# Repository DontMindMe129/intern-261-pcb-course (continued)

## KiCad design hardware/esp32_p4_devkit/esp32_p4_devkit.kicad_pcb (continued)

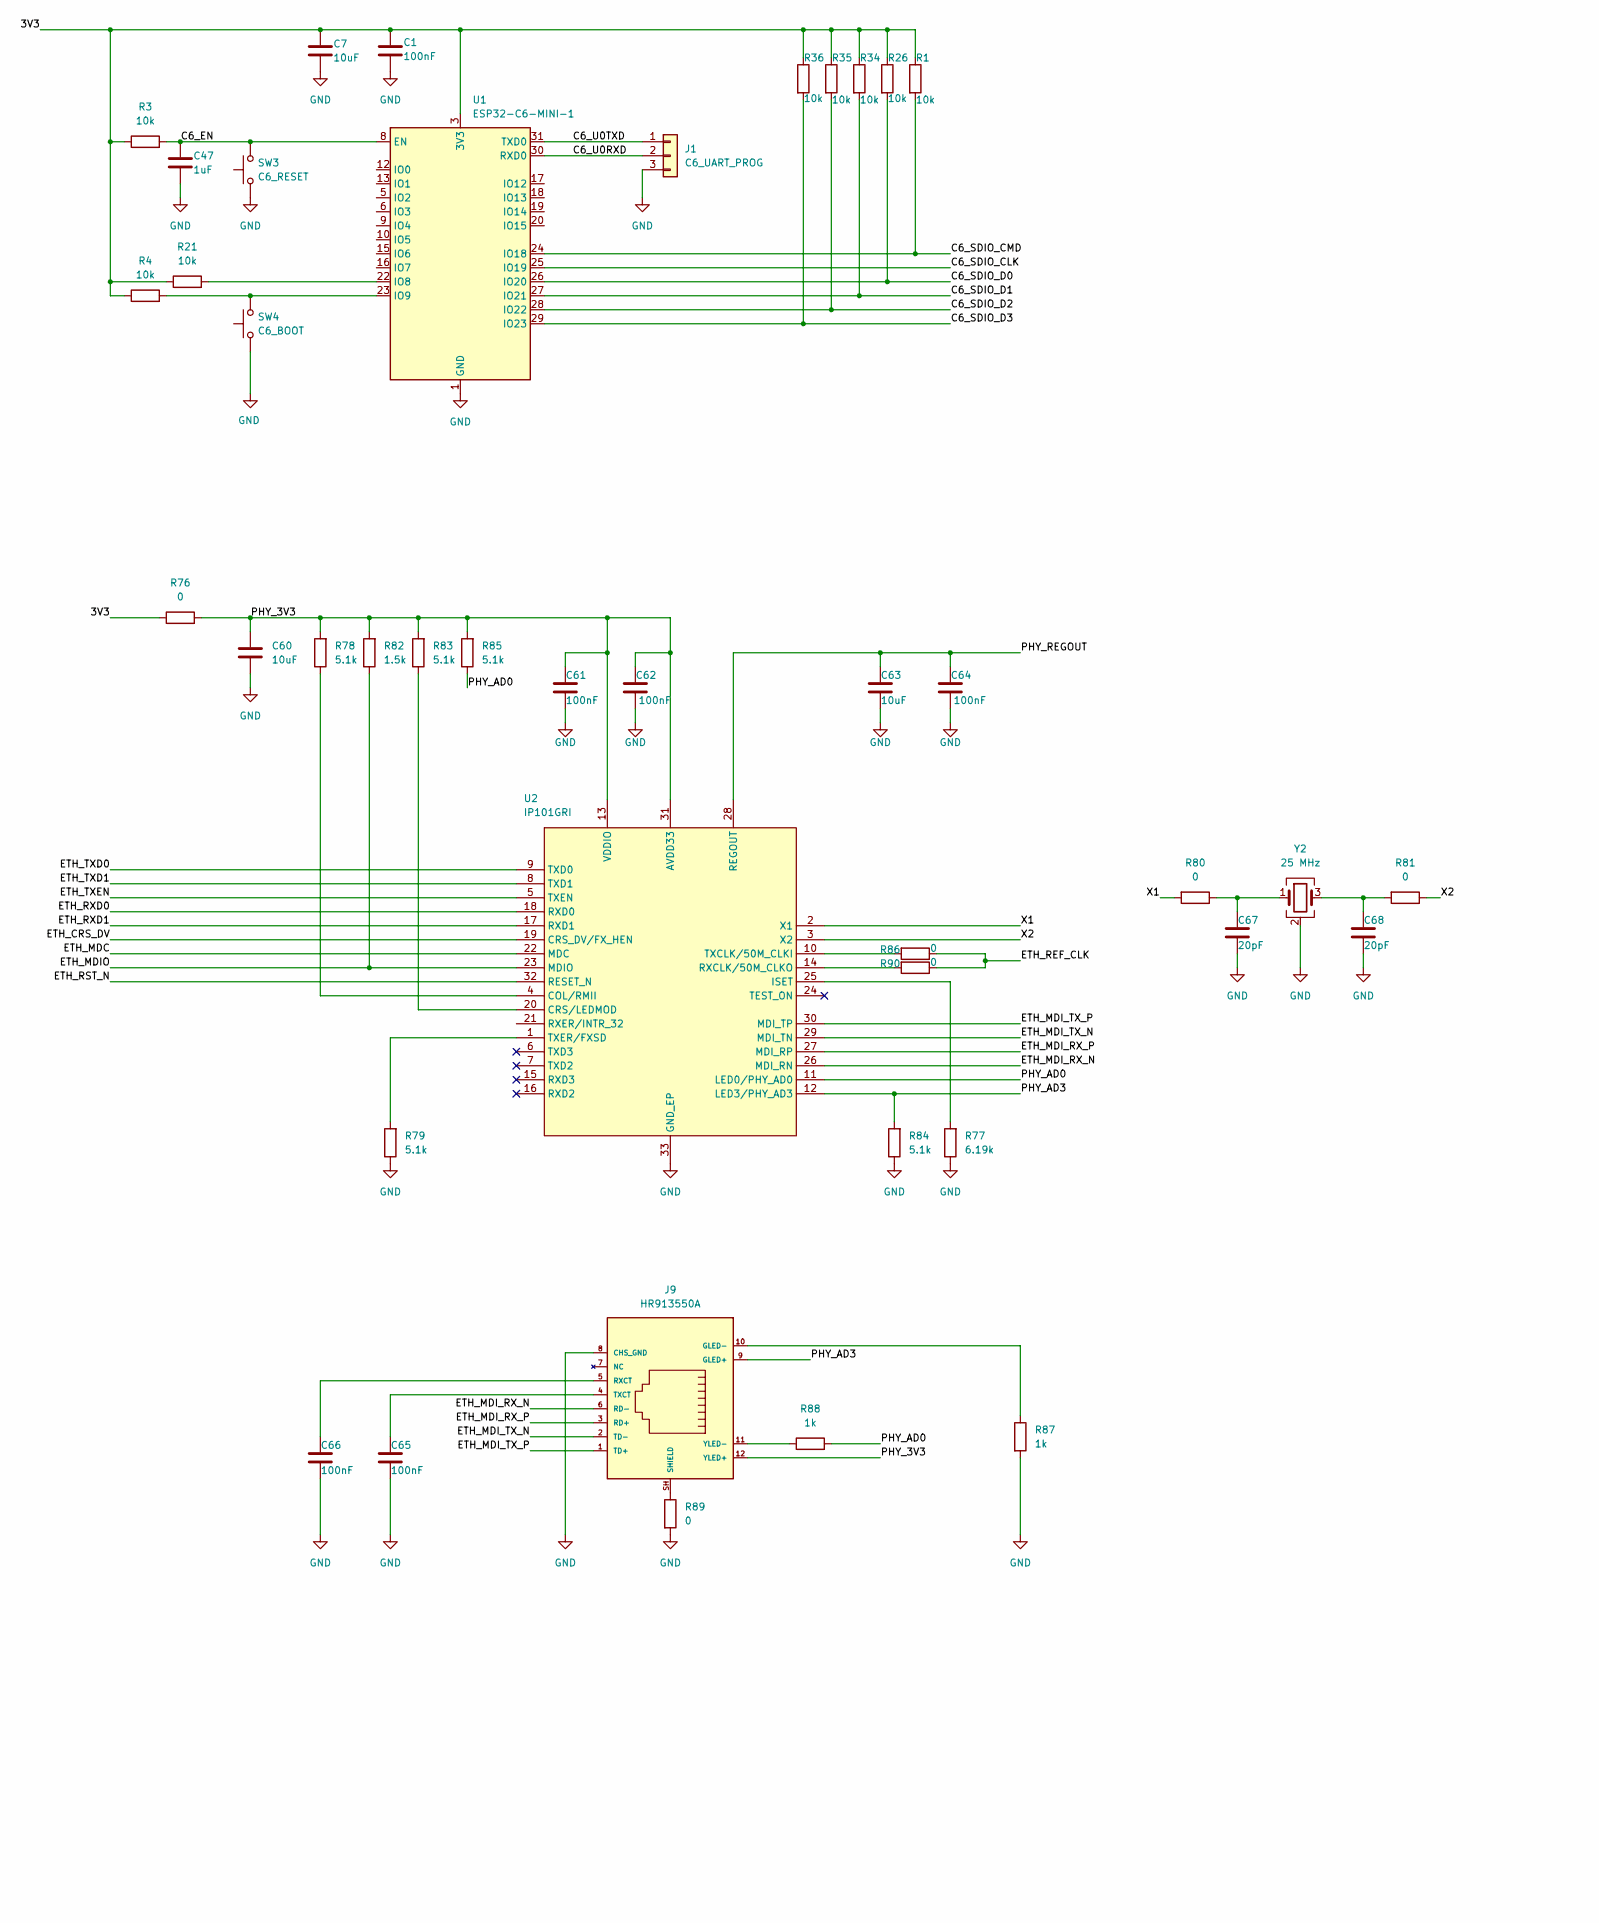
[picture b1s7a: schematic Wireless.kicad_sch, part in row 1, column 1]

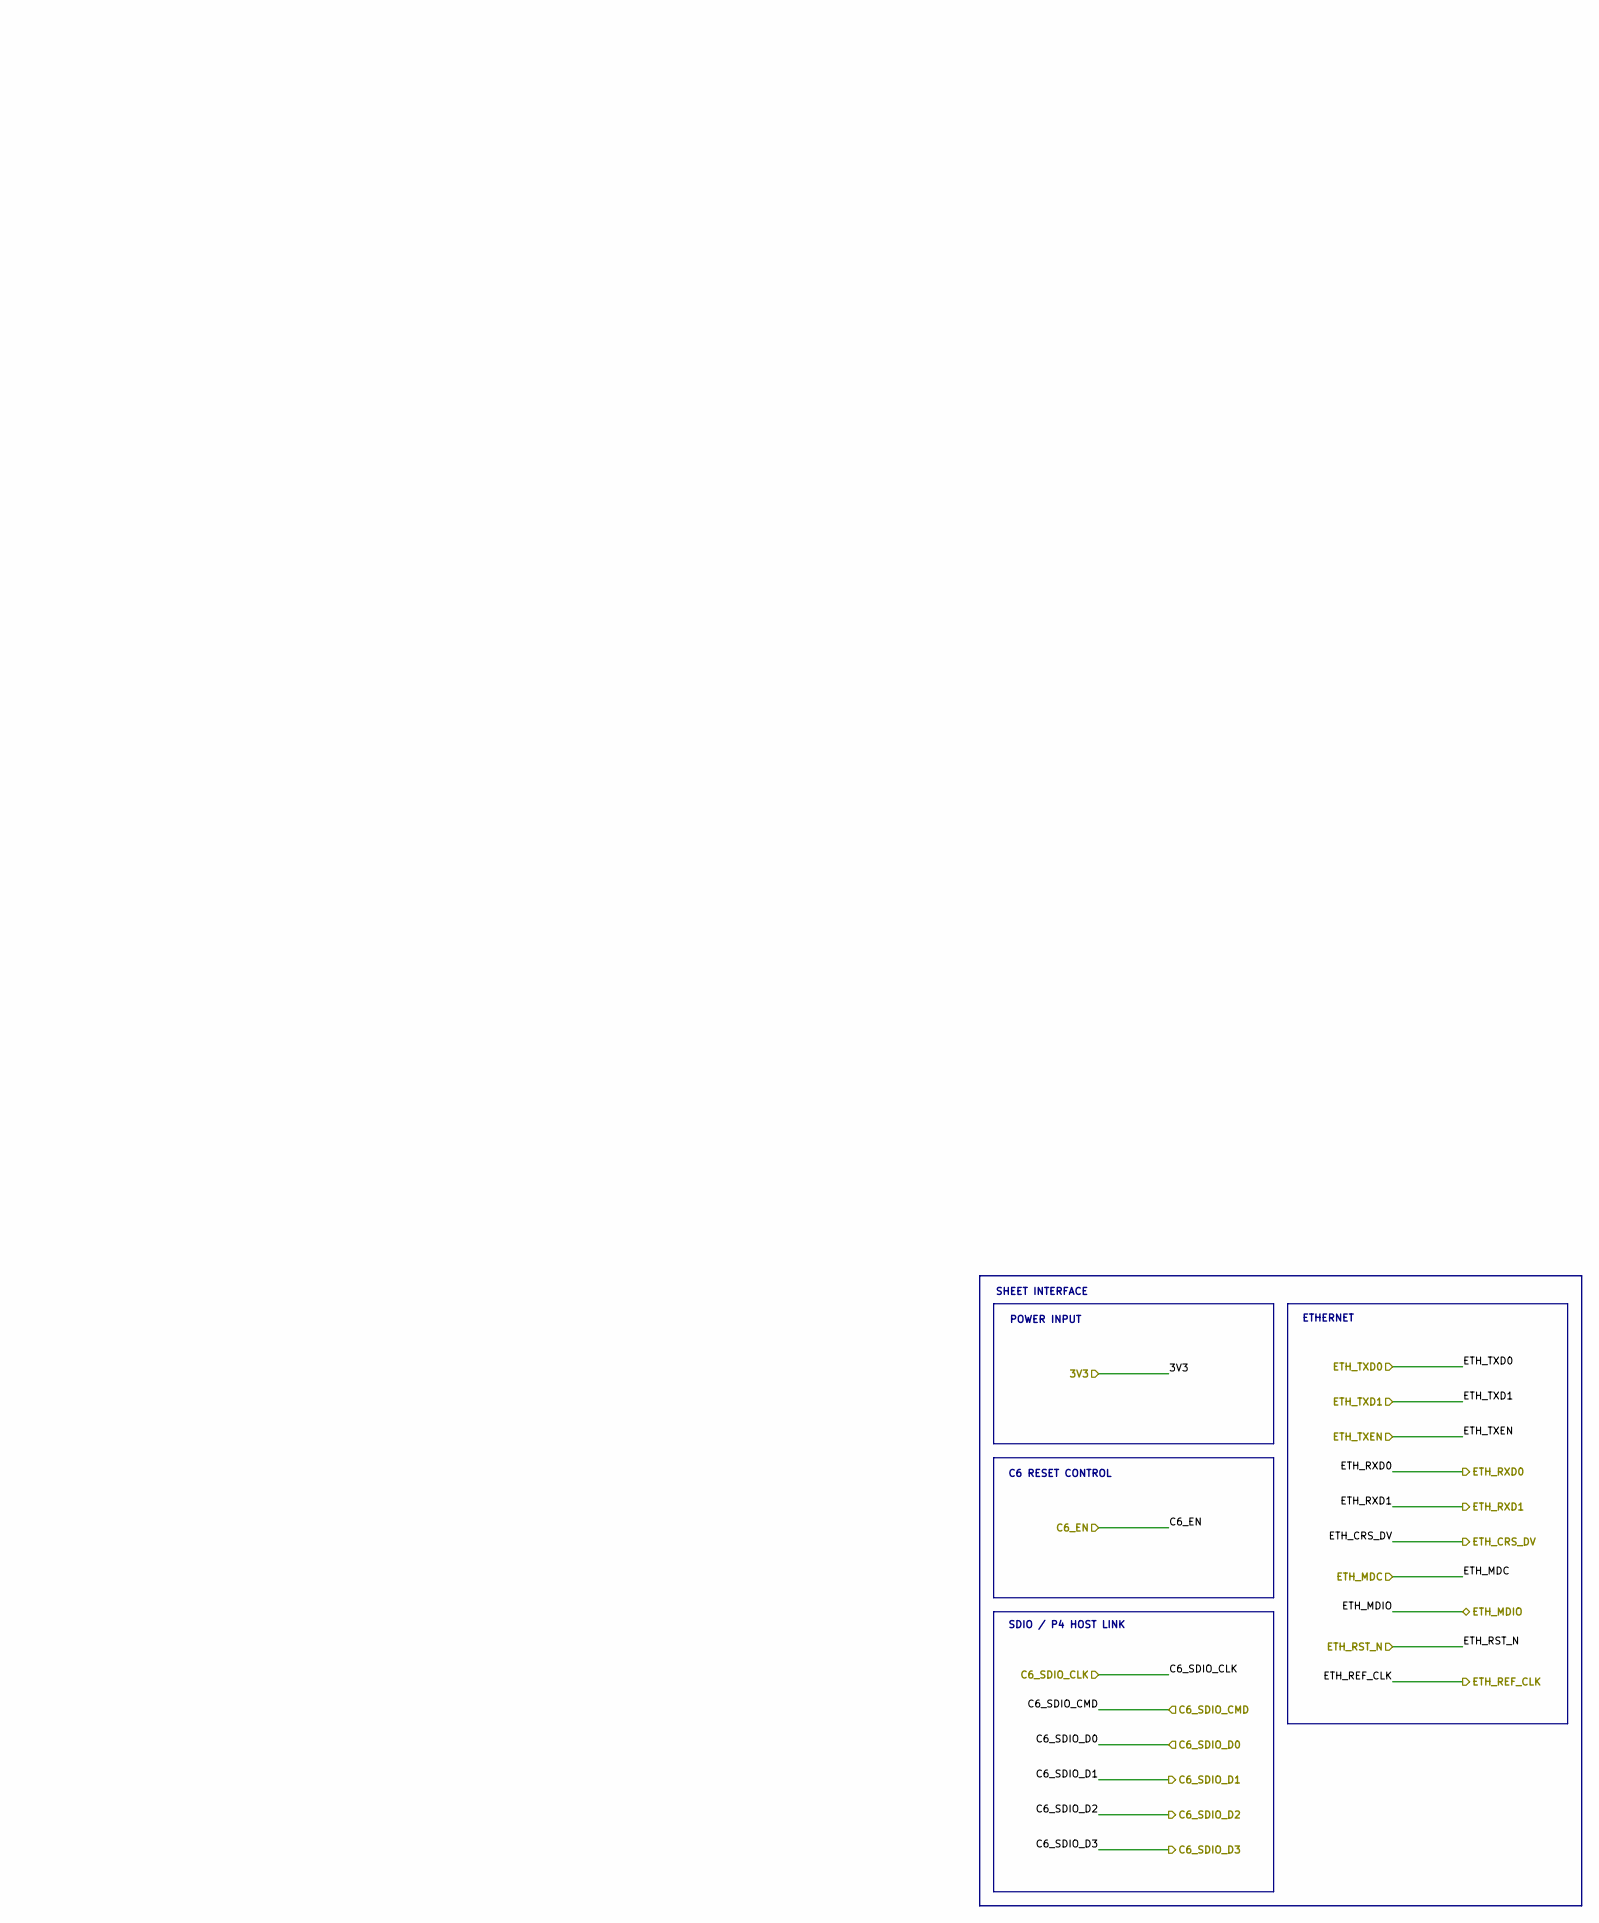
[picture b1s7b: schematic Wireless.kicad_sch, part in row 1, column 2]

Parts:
C1, C61, C62, C64: 100nF; C_0402_1005Metric; MPN CL05B104KO5NNNC
C7, C60, C63: 10uF; C_1206_3216Metric; MPN GRM31CR71E106MA12L
C47: 1uF; C_0805_2012Metric; MPN GRM21BR71C105KA01L
C65, C66: 100nF; C_0603_1608Metric; MPN CL10B104KB8NFNC
C67, C68: 20pF; C_0603_1608Metric; MPN CL10C200JB8NNNC
J1: C6_UART_PROG; PinHeader_1x03_P2.54mm_Vertical
J9: HR913550A; MPN HR913550A
R1, R3, R4, R21, R26, R34, R35, R36: 10k; R_0603_1608Metric; MPN ERJ-3EKF1002V
R76, R80, R81, R86, R89, R90: 0; R_0603_1608Metric; MPN ERJ-3GEY0R00V
R77: 6.19k; R_0603_1608Metric; MPN CRCW06036K19FKEA
R78, R79, R83, R84, R85: 5.1k; R_0603_1608Metric; MPN CRCW06035K10FKEA
R82: 1.5k; R_0603_1608Metric; MPN CRCW06031K50FKEA
R87, R88: 1k; R_0603_1608Metric; MPN ERJ-3EKF1001V
SW3: C6_RESET; SW_SPST_TL3305A; MPN TL3305AF160QG
SW4: C6_BOOT; SW_SPST_TL3305A; MPN TL3305AF160QG
U1: ESP32-C6-MINI-1; MPN ESP32-C6-MINI-1-N4
U2: IP101GRI; QFN-32-1EP_4x4mm_P0.4mm_EP2.65x2.65mm; MPN IP101GRI
Y2: 25 MHz; Crystal_SMD_3225-4Pin_3.2x2.5mm; MPN ECS-250-12-33Q-JES-TR

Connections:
/3V3: C1.1, C7.1, R1.1, R3.1, R4.1, R21.1, R26.1, R34.1, R35.1, R36.1, R76.1, U1.3 (3V3); also elsewhere on the board
/C6_EN: C47.1, R3.2, SW3.2, U1.8 (EN); also elsewhere on the board
/C6_SDIO_CLK: U1.25 (IO19); also elsewhere on the board
/C6_SDIO_CMD: R1.2, U1.24 (IO18); also elsewhere on the board
/C6_SDIO_D0: R26.2, U1.26 (IO20); also elsewhere on the board
/C6_SDIO_D1: R34.2, U1.27 (IO21); also elsewhere on the board
/C6_SDIO_D2: R35.2, U1.28 (IO22); also elsewhere on the board
/C6_SDIO_D3: R36.2, U1.29 (IO23); also elsewhere on the board
/Connectivity/C6_U0RXD: J1.2, U1.30 (RXD0)
/Connectivity/C6_U0TXD: J1.1, U1.31 (TXD0)
/Connectivity/ETH_MDI_RX_N: J9.6 (RD-), U2.26 (MDI_RN)
/Connectivity/ETH_MDI_RX_P: J9.3 (RD+), U2.27 (MDI_RP)
/Connectivity/ETH_MDI_TX_N: J9.2 (TD-), U2.29 (MDI_TN)
/Connectivity/ETH_MDI_TX_P: J9.1 (TD+), U2.30 (MDI_TP)
/Connectivity/PHY_3V3: C60.1, C61.1, C62.1, J9.12 (YLED+), R76.2, R78.2, R82.2, R83.2, R85.2, U2.13 (VDDIO), U2.31 (AVDD33)
/Connectivity/PHY_AD0: R85.1, R88.2, U2.11 (LED0/PHY_AD0)
/Connectivity/PHY_AD3: J9.9 (GLED+), R84.2, U2.12 (LED3/PHY_AD3)
/Connectivity/PHY_REGOUT: C63.1, C64.1, U2.28 (REGOUT)
/Connectivity/X1: R80.2, U2.2 (X1)
/Connectivity/X2: R81.1, U2.3 (X2)
/ETH_CRS_DV: U2.19 (CRS_DV/FX_HEN); also elsewhere on the board
/ETH_MDC: U2.22 (MDC); also elsewhere on the board
/ETH_MDIO: R82.1, U2.23 (MDIO); also elsewhere on the board
/ETH_REF_CLK: R86.1, R90.1; also elsewhere on the board
/ETH_RST_N: U2.32 (RESET_N); also elsewhere on the board
/ETH_RXD0: U2.18 (RXD0); also elsewhere on the board
/ETH_RXD1: U2.17 (RXD1); also elsewhere on the board
/ETH_TXD0: U2.9 (TXD0); also elsewhere on the board
/ETH_TXD1: U2.8 (TXD1); also elsewhere on the board
/ETH_TXEN: U2.5 (TXEN); also elsewhere on the board
GND: C1.2, C7.2, C47.2, C60.2, C61.2, C62.2, C63.2, C64.2, C65.2, C66.2, C67.2, C68.2, J1.3, J9.8 (CHS_GND), R77.1, R79.1, R84.1, R87.2, R89.2, SW3.1, SW4.1, U1.1 (GND), U1.2 (GND), U1.11 (GND), U1.14 (GND), U1.36 (GND), U1.37 (GND), U1.38 (GND), U1.39 (GND), U1.40 (GND), U1.41 (GND), U1.42 (GND), U1.43 (GND), U1.44 (GND), U1.45 (GND), U1.46 (GND), U1.47 (GND), U1.48 (GND), U1.49 (GND), U1.50 (GND), U1.51 (GND), U1.52 (GND), U1.53 (GND), U2.33 (GND_EP), Y2.2 (G), Y2.4 (G); also elsewhere on the board
unnamed: C67.1, R80.1, Y2.1
unnamed: C68.1, R81.2, Y2.3
unnamed: J9.10 (GLED-), R87.1
unnamed: C66.1, J9.5 (RXCT)
unnamed: J9.SH (SHIELD), R89.1
unnamed: C65.1, J9.4 (TXCT)
unnamed: J9.11 (YLED-), R88.1
unnamed: R21.2, U1.22 (IO8)
unnamed: R4.2, SW4.2, U1.23 (IO9)
unnamed: R78.1, U2.4 (COL/RMII)
unnamed: R83.1, U2.20 (CRS/LEDMOD)
unnamed: R77.2, U2.25 (ISET)
unnamed: R90.2, U2.14 (RXCLK/50M_CLKO)
unnamed: R86.2, U2.10 (TXCLK/50M_CLKI)
unnamed: R79.2, U2.1 (TXER/FXSD)

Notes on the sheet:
SHEET INTERFACE
C6 RESET CONTROL
SDIO / P4 HOST LINK
ETHERNET
POWER INPUT

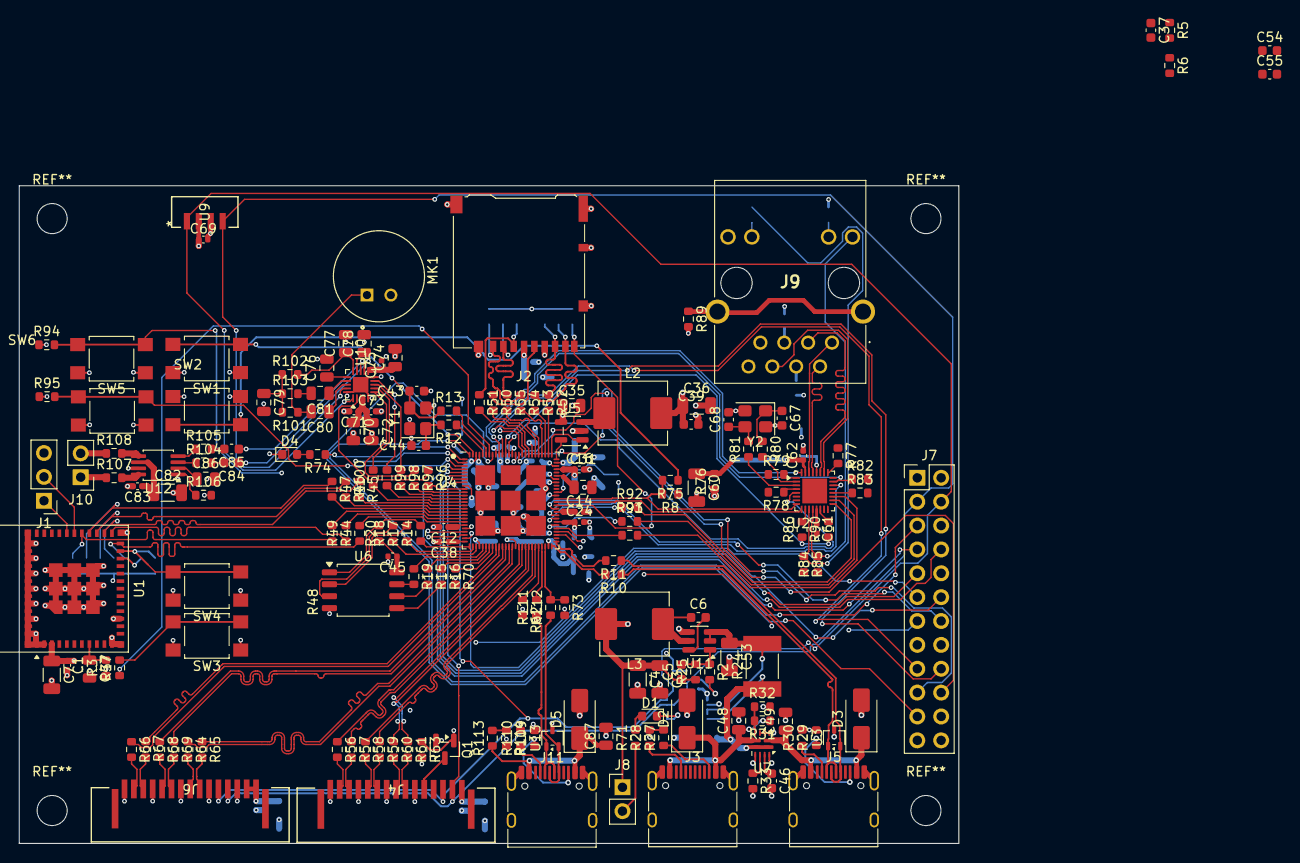
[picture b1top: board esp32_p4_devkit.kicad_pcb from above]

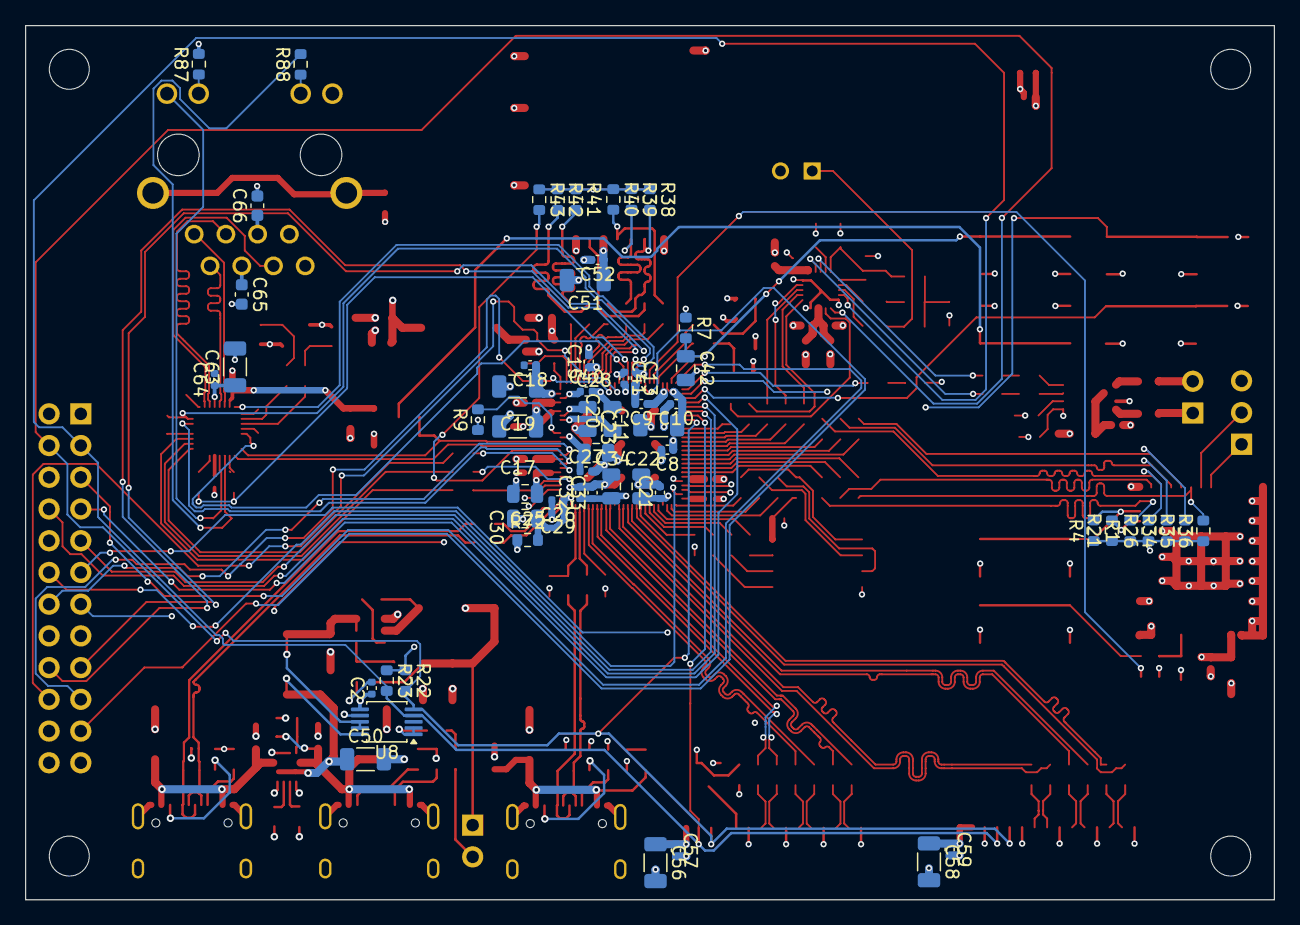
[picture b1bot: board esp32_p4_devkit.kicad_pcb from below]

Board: 4 copper layers, 100.0 x 70.0 mm, 242 parts (58 on the bottom side), 201 nets.
